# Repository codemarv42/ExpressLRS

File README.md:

# ExpressLRS

ExpressLRS is an open source project that enables the connection between drone and remote control in an efficient way. To support the project itself a little bit, I have developed other hardware alternatives, which are of course also open source. To support the project visit: https://github.com/ExpressLRS/ExpressLRS

Parameter for TX Mini REV1:

- Layer: 2
- Thickness: 1,2mm
- Minimum Copper Trace Width: 0.15mm

## Improvements

> - [ ] Pin 0 (Boot) to GND Pad for initial upload of the program

Parameter for RX Nano REV1:

- Layer: 4
- Thickness: 1,2mm / 1mm
- Minimum Copper Trace Width: 0.09mm

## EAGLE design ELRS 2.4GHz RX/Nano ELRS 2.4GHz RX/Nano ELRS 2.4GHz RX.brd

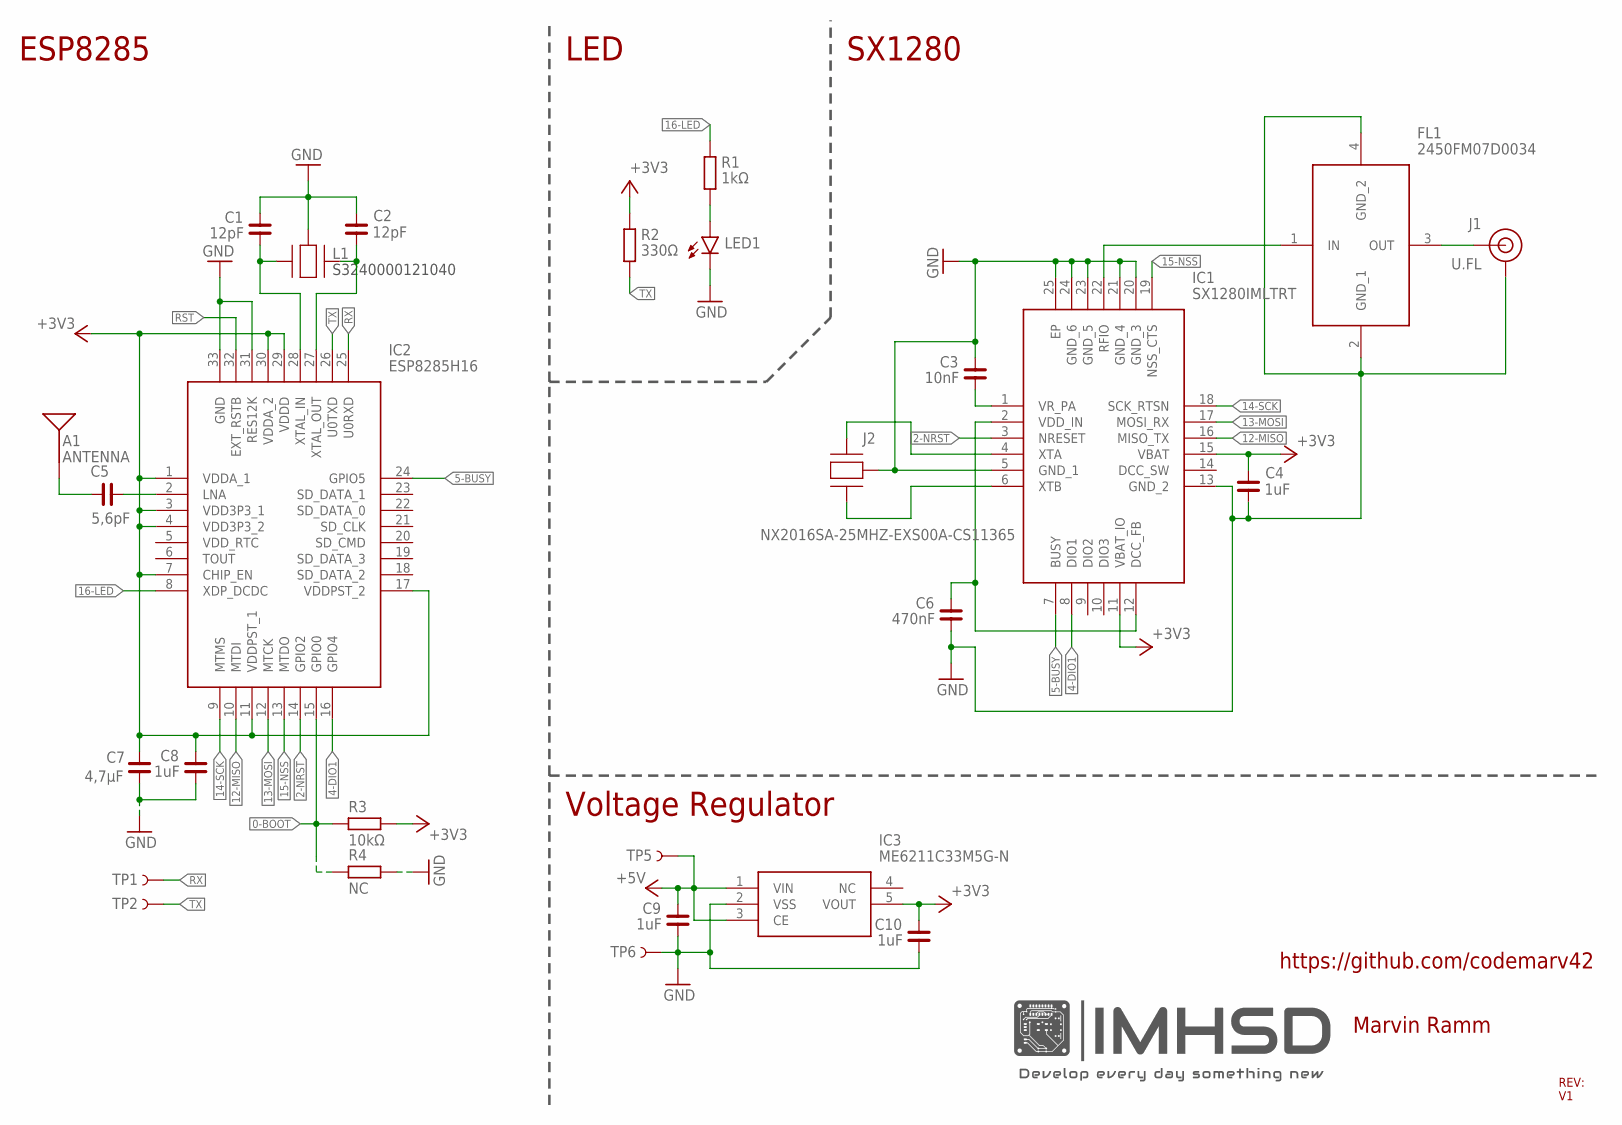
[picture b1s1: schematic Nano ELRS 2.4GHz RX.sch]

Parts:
A1: ANTENNA; TRACE_ANTENNA_2.4GHZ_NANO
C1, C2: 12pF; C0402
C3: 10nF; C0402
C4, C8, C9, C10: 1uF; C0402
C5: 5,6pF; C0402
C6: 470nF; C0402
C7: 4,7µF; C0603
FL1: 2450FM07D0034
IC1: SX1280IMLTRT; QFN50P400X400X100-25N
IC2: ESP8285H16; QFN50P500X500X90-33N
IC3: ME6211C33M5G-N; SOT95P270X145-5N
J1: U.FL
J2: NX2016SA-25MHZ-EXS00A-CS11365; NX2016SA25MHZEXS00ACS11365
L1: SMD-3225_4P16MHZ_20PF_10PPM_-4; SMD3225_4P16MHZ20PF10PPM4085
LED1: SZYY0603W; CHIP-LED0603
R1: 1kΩ; R0402
R2: 330Ω; R0402
R3: 10kΩ; R0402
R4: NC; R0402
TP1, TP2, TP5, TP6: TEST-POINT3X5; PAD.03X.05

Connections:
0-BOOT: IC2.15 (GPIO0), R3.2, R4.2
2-NRST: IC1.3 (NRESET), IC2.14 (GPIO2)
4-DIO1: IC1.8 (DIO1), IC2.16 (GPIO4)
5-BUSY: IC1.7 (BUSY), IC2.24 (GPIO5)
12-MISO: IC1.16 (MISO_TX), IC2.10 (MTDI)
13-MOSI: IC1.17 (MOSI_RX), IC2.12 (MTCK)
14-SCK: IC1.18 (SCK_RTSN), IC2.9 (MTMS)
15-NSS: IC1.19 (NSS_CTS), IC2.13 (MTDO)
16-LED: IC2.8 (XDP_DCDC), R1.1
+3V3: C4.1, C7.1, C8.1, C10.1, IC1.11 (VBAT_IO), IC1.15 (VBAT), IC2.1 (VDDA_1), IC2.3 (VDD3P3_1), IC2.4 (VDD3P3_2), IC2.7 (CHIP_EN), IC2.11 (VDDPST_1), IC2.17 (VDDPST_2), IC2.29 (VDDD), IC2.30 (VDDA_2), IC3.5 (VOUT), R2.1, R3.1
+5V: C9.1, IC3.1 (VIN), IC3.3 (CE), TP5.1
GND: C1.1, C2.1, C3.1, C4.2, C6.2, C7.2, C8.2, C9.2, C10.2, FL1.2 (GND_1), FL1.4 (GND_2), IC1.5 (GND_1), IC1.13 (GND_2), IC1.20 (GND_3), IC1.21 (GND_4), IC1.23 (GND_5), IC1.24 (GND_6), IC1.25 (EP), IC2.31 (RES12K), IC2.33 (GND), IC3.2 (VSS), J1.1 (GND), J1.2 (GND), J2.2 (GND_2), J2.4 (GND_2), L1.2 (GND_2), L1.4 (GND_2), LED1.C, R4.1, TP6.1
unnamed: C1.2, IC2.28 (XTAL_IN), L1.1 (CRYSTAL_1)
unnamed: C3.2, IC1.1 (VR_PA)
unnamed: C2.2, IC2.27 (XTAL_OUT), L1.3 (CRYSTAL_2)
unnamed: C5.1, IC2.2 (LNA)
unnamed: A1.ANT, C5.2
unnamed: C6.1, IC1.2 (VDD_IN), IC1.12 (DCC_FB)
unnamed: IC1.6 (XTB), J2.3 (CRYSTAL_2)
unnamed: IC1.4 (XTA), J2.1 (CRYSTAL_1)
unnamed: FL1.1 (IN), IC1.22 (RFIO)
unnamed: FL1.3 (OUT), J1.FEED (SIGNAL)
unnamed: LED1.A, R1.2
RST: IC2.32 (EXT_RSTB)
RX: IC2.25 (U0RXD), TP1.1
TX: IC2.26 (U0TXD), R2.2, TP2.1

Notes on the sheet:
S3240000121040
Marvin Ramm
ESP8285
LED
SX1280
Voltage Regulator
REV: V1
https://github.com/codemarv42

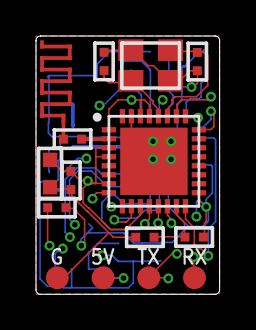
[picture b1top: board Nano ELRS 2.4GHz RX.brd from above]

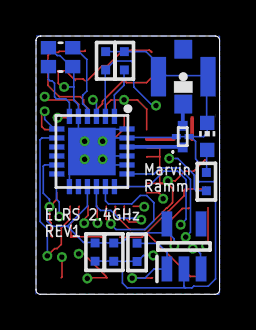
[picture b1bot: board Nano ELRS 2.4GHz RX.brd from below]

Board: 4 copper layers, 10.2 x 14.3 mm, 27 parts (12 on the bottom side), 25 nets.

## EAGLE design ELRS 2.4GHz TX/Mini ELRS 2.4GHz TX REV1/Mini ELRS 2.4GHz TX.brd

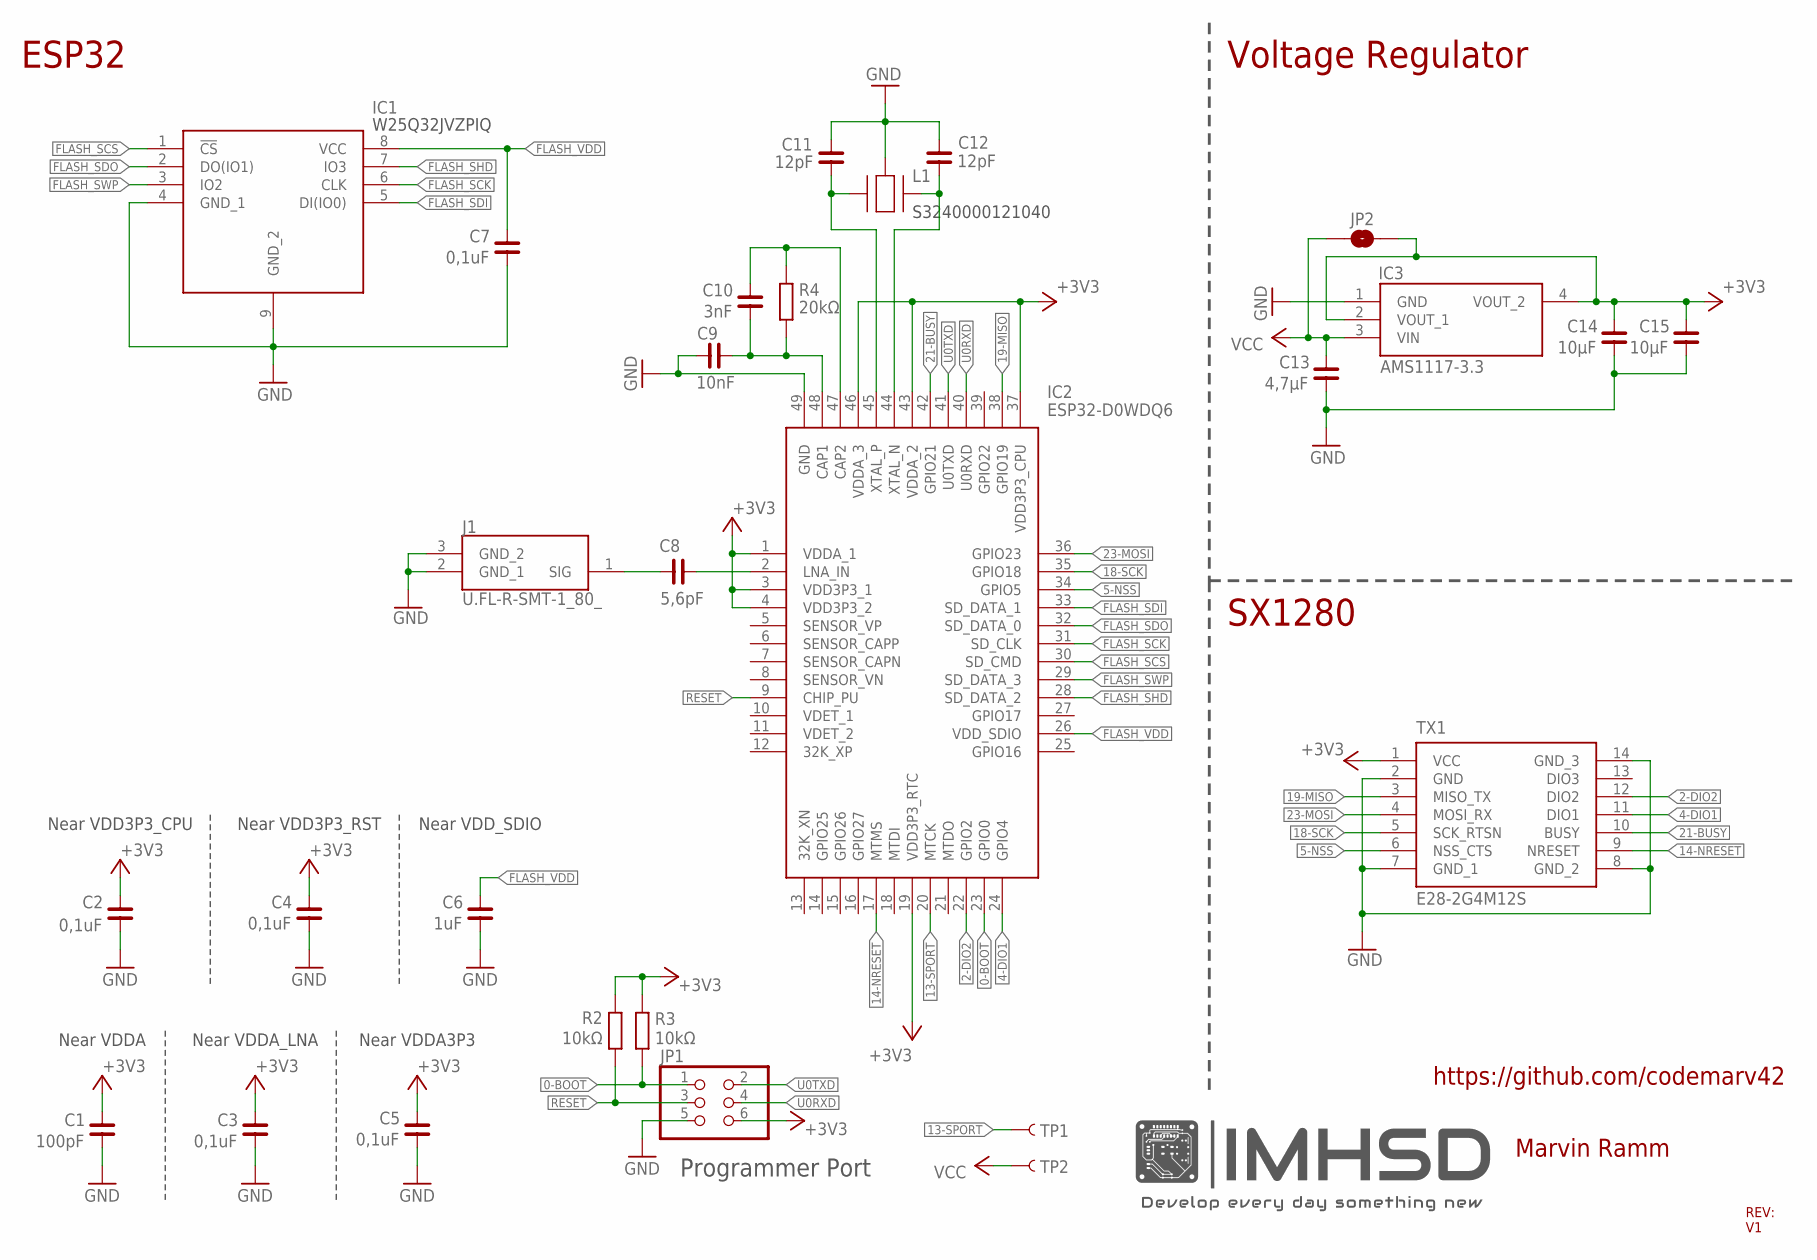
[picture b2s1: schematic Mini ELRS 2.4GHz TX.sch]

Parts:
C1: 100pF; C0402
C2, C3, C4, C5, C7: 0,1uF; C0402
C6: 1uF; C0402
C8: 5,6pF; C0402
C9: 10nF; C0402
C10: 3nF; C0402
C11, C12: 12pF; C0402
C13: 4,7µF; C0603
C14, C15: 10µF; C0603
IC1: W25Q128JVPIQ; SON127P800X600X80-9N
IC2: ESP32-D0WDQ6; QFN40P600X600X90-49N
IC3: AMS1117-3.3; SOT229P700X180-4N
J1: U.FL-R-SMT-1_80_; UFLRSMT180
JP1: ESP32_PRG_PORT
JP2: JUMPER-SMT_2_NO_SILK; SMT-JUMPER_2_NO_SILK
L1: SMD-3225_4P16MHZ_20PF_10PPM_-4; SMD3225_4P16MHZ20PF10PPM4085
R2, R3: 10kΩ; R0402
R4: 20kΩ; R0402
TP1, TP2: TEST-POINT3X5; PAD.03X.05
TX1: E28-2G4M12S

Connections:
0-BOOT: IC2.23 (GPIO0), JP1.1, R3.2
2-DIO2: IC2.22 (GPIO2), TX1.12 (DIO2)
4-DIO1: IC2.24 (GPIO4), TX1.11 (DIO1)
5-NSS: IC2.34 (GPIO5), TX1.6 (NSS_CTS)
13-SPORT: IC2.20 (MTCK), TP1.1
14-NRESET: IC2.17 (MTMS), TX1.9 (NRESET)
18-SCK: IC2.35 (GPIO18), TX1.5 (SCK_RTSN)
19-MISO: IC2.38 (GPIO19), TX1.3 (MISO_TX)
21-BUSY: IC2.42 (GPIO21), TX1.10 (BUSY)
23-MOSI: IC2.36 (GPIO23), TX1.4 (MOSI_RX)
+3V3: C1.2, C2.2, C3.2, C4.2, C5.2, C14.1, C15.1, IC2.1 (VDDA_1), IC2.3 (VDD3P3_1), IC2.4 (VDD3P3_2), IC2.19 (VDD3P3_RTC), IC2.37 (VDD3P3_CPU), IC2.43 (VDDA_2), IC2.46 (VDDA_3), IC3.2 (VOUT_1), IC3.4 (VOUT_2), JP1.6, JP2.2, R2.2, R3.1, TX1.1 (VCC)
FLASH_SCK: IC1.6 (CLK), IC2.31 (SD_CLK)
FLASH_SCS: IC1.1 (!CS), IC2.30 (SD_CMD)
FLASH_SDI: IC1.5 (DI(IO0)), IC2.33 (SD_DATA_1)
FLASH_SDO: IC1.2 (DO(IO1)), IC2.32 (SD_DATA_0)
FLASH_SHD: IC1.7 (IO3), IC2.28 (SD_DATA_2)
FLASH_SWP: IC1.3 (IO2), IC2.29 (SD_DATA_3)
FLASH_VDD: C6.2, C7.2, IC1.8 (VCC), IC2.26 (VDD_SDIO)
GND: C1.1, C2.1, C3.1, C4.1, C5.1, C6.1, C7.1, C9.1, C11.1, C12.1, C13.2, C14.2, C15.2, IC1.4 (GND_1), IC1.9 (GND_2), IC2.49 (GND), IC3.1 (GND), J1.2 (GND_1), J1.3 (GND_2), JP1.5, L1.2 (GND_2), L1.4 (GND_2), TX1.2 (GND), TX1.7 (GND_1), TX1.8 (GND_2), TX1.14 (GND_3)
unnamed: C8.2, J1.1 (SIG)
unnamed: C8.1, IC2.2 (LNA_IN)
unnamed: C9.2, C10.1, IC2.48 (CAP1), R4.2
unnamed: C10.2, IC2.47 (CAP2), R4.1
unnamed: C12.2, IC2.44 (XTAL_N), L1.3 (CRYSTAL_2)
unnamed: C11.2, IC2.45 (XTAL_P), L1.1 (CRYSTAL_1)
RESET: IC2.9 (CHIP_PU), JP1.3, R2.1
U0RXD: IC2.40 (U0RXD), JP1.4
U0TXD: IC2.41 (U0TXD), JP1.2
VCC: C13.1, IC3.3 (VIN), JP2.1, TP2.1

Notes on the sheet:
S3240000121040
Near VDDA
Near VDDA_LNA
Near VDDA3P3
Near VDD3P3_CPU
Near VDD3P3_RST
Near VDD_SDIO
Programmer Port
W25Q32JVZPIQ
Marvin Ramm
REV: V1
https://github.com/codemarv42
ESP32
Voltage Regulator
SX1280

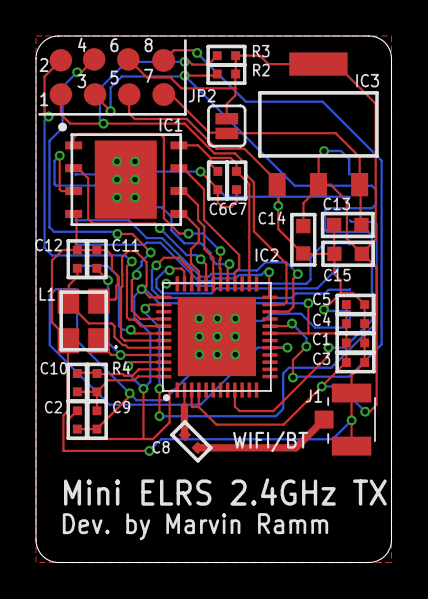
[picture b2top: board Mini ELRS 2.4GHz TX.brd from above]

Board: 2 copper layers, 19.8 x 29.2 mm, 28 parts (1 on the bottom side), 29 nets.

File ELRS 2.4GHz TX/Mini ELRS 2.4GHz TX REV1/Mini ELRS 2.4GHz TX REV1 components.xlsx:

Mini ELRS 2.4GHz TX REV1 components
Row | Annotations | Type | Nr | LCSC Nr | Anz
1 | IC1 | Flash Memory 4MB | W25Q32JVZPIQ |  | 1
2 | IC2 | ESP32 | ESP32-D0WDQ6 |  | 1
3 | J1 |  | U.FL-R-SMD |  | 1
4 | L1 |  | S3240000121040 |  | 1
5 | TX1 |  | E28-2G4M12S |  | 1
6 | IC3 | 3.3V 1A Voltage regulator | AMS1117-3.3 |  | 1
7
8
9
10
11
12
13
14
15
16
17
18
19
 | Resistors & Condensators
20 | C2, C4, C3, C5, C7 | 100NF 16V 0402 |  |  | 5
21 | C6 | 1uF 16V 0402 |  |  | 1
22 | C13 | 4,7uF 0603 |  |  | 1
23 | C14, C15 | 10uF 0603 |  |  | 2
24 | C1 | 100pF 0402 |  |  | 1
25 | C11, C12 | 12pF 0402 |  |  | 2
26 | C10 | 3nF 0402 |  |  | 1
27 | C9 | 10nF 0402 |  |  | 1
28 | C8 | 5,6pF 0402 |  |  | 1
29 | R2, R3 | 10kOhm 0402 |  |  | 2
30 | R4 | 20kOhm 0402 |  |  | 1
31

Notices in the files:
parts and their libraries:
SparkFun-RF: Licensing: Creative Commons ShareAlike 4.0 International - https://creativecommons.org/licenses/by-sa/4.0
rc-master-smd: Copyright (C) 2007, Bob Starr
